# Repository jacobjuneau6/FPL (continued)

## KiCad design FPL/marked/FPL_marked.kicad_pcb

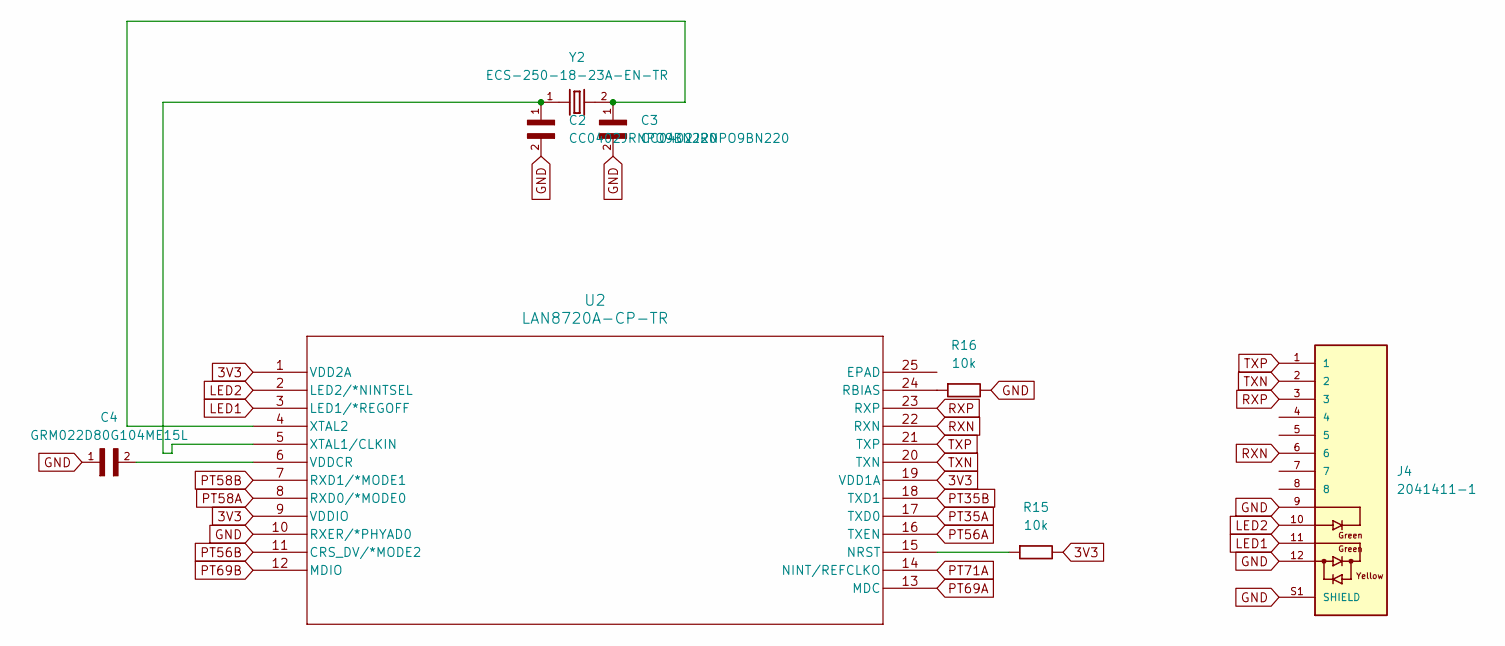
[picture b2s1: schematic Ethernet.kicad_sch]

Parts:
C2, C3: CC0402JRNPO9BN220; CAPC1005X55N; DigiKey_Part_Number 311-1018-1-ND
C4: GRM022D80G104ME15L; CAPC0402X22N; DigiKey_Part_Number 490-10386-1-ND
J4: 2041411-1; TE_2041411-1; PARTREV A; DigiKey_Part_Number A135635CT-ND
R15, R16: 10k; R_Axial_DIN0207_L6.3mm_D2.5mm_P10.16mm_Horizontal
U2: LAN8720A-CP-TR; QFN24-6X6_MC_MCH
Y2: ECS-250-18-23A-EN-TR; XTAL_ECS-250-18-23A-EN-TR; DigiKey_Part_Number XC1671CT-ND

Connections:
3V3: R15.2, U2.1 (VDD2A), U2.9 (VDDIO), U2.19 (VDD1A); also elsewhere on the board
GND: C2.2, C3.2, C4.1, J4.9, J4.12, J4.S1 (SHIELD), J4.S2 (SHIELD), R16.2, U2.10 (RXER/*PHYAD0); also elsewhere on the board
LED1: J4.11, U2.3 (LED1/*REGOFF)
LED2: J4.10, U2.2 (LED2/*NINTSEL)
unnamed: R15.1, U2.15 (NRST)
unnamed: R16.1, U2.24 (RBIAS)
unnamed: C4.2, U2.6 (VDDCR)
unnamed: C2.1, U2.5 (XTAL1/CLKIN), Y2.1
unnamed: C3.1, U2.4 (XTAL2), Y2.2
PT35A: U2.17 (TXD0); also elsewhere on the board
PT35B: U2.18 (TXD1); also elsewhere on the board
PT56A: U2.16 (TXEN); also elsewhere on the board
PT56B: U2.11 (CRS_DV/*MODE2); also elsewhere on the board
PT58A: U2.8 (RXD0/*MODE0); also elsewhere on the board
PT58B: U2.7 (RXD1/*MODE1); also elsewhere on the board
PT69A: U2.13 (MDC); also elsewhere on the board
PT69B: U2.12 (MDIO); also elsewhere on the board
PT71A: U2.14 (NINT/REFCLKO); also elsewhere on the board
RXN: J4.6, U2.22 (RXN)
RXP: J4.3, U2.23 (RXP)
TXN: J4.2, U2.20 (TXN)
TXP: J4.1, U2.21 (TXP)

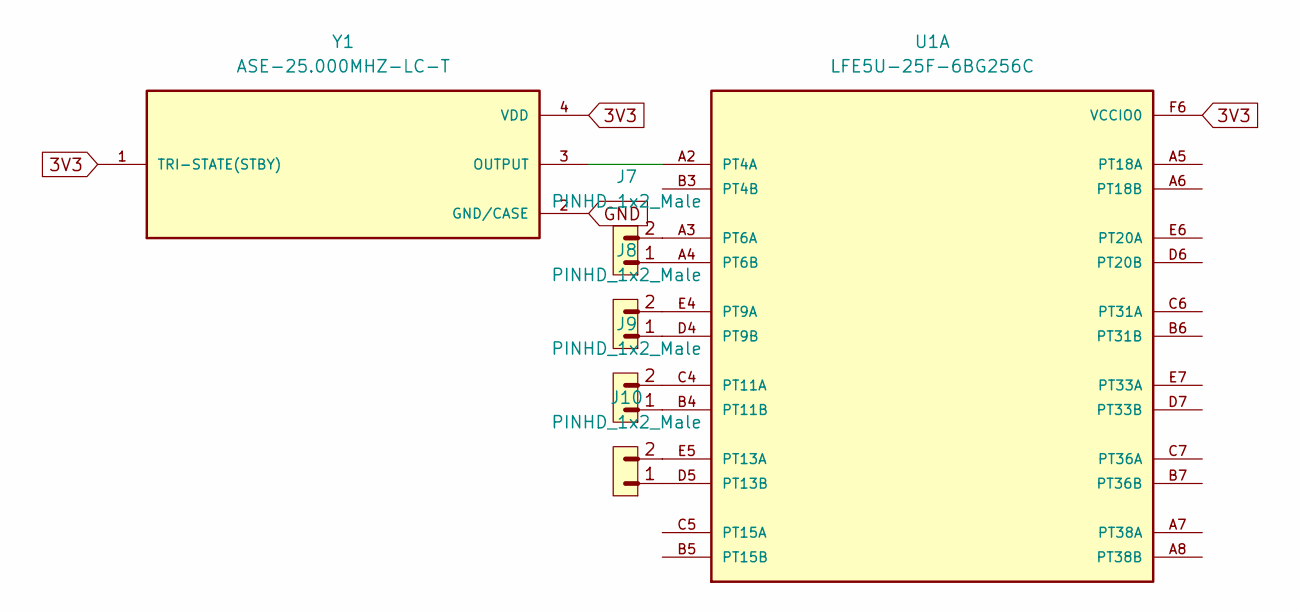
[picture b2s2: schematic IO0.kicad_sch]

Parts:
J7, J8, J9, J10: PINHD_1x2_Male; PinHeader_1x02_P2.54mm_Vertical
U1: LFE5U-25F-6BG256C; BGA256C80P16X16_1400X1400X170; PARTREV 2.8; DigiKey_Part_Number 220-2205-ND
Y1: ASE-25.000MHZ-LC-T; XTAL_ASE-25.000MHZ-LC-T; PARTREV 02-18-22; DigiKey_Part_Number 535-ASE-25.000MHZ-L-C-TCT-ND

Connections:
3V3: U1.F6 (VCCIO0), U1.F7 (VCCIO0), Y1.1 (TRI-STATE(STBY)), Y1.4 (VDD); also elsewhere on the board
GND: Y1.2 (GND/CASE); also elsewhere on the board
unnamed: U1.A2 (PT4A), Y1.3 (OUTPUT)
unnamed: J7.2, U1.A3 (PT6A)
unnamed: J7.1, U1.A4 (PT6B)
unnamed: J8.2, U1.E4 (PT9A)
unnamed: J8.1, U1.D4 (PT9B)
unnamed: J9.2, U1.C4 (PT11A)
unnamed: J9.1, U1.B4 (PT11B)
unnamed: J10.2, U1.E5 (PT13A)
unnamed: J10.1, U1.D5 (PT13B)

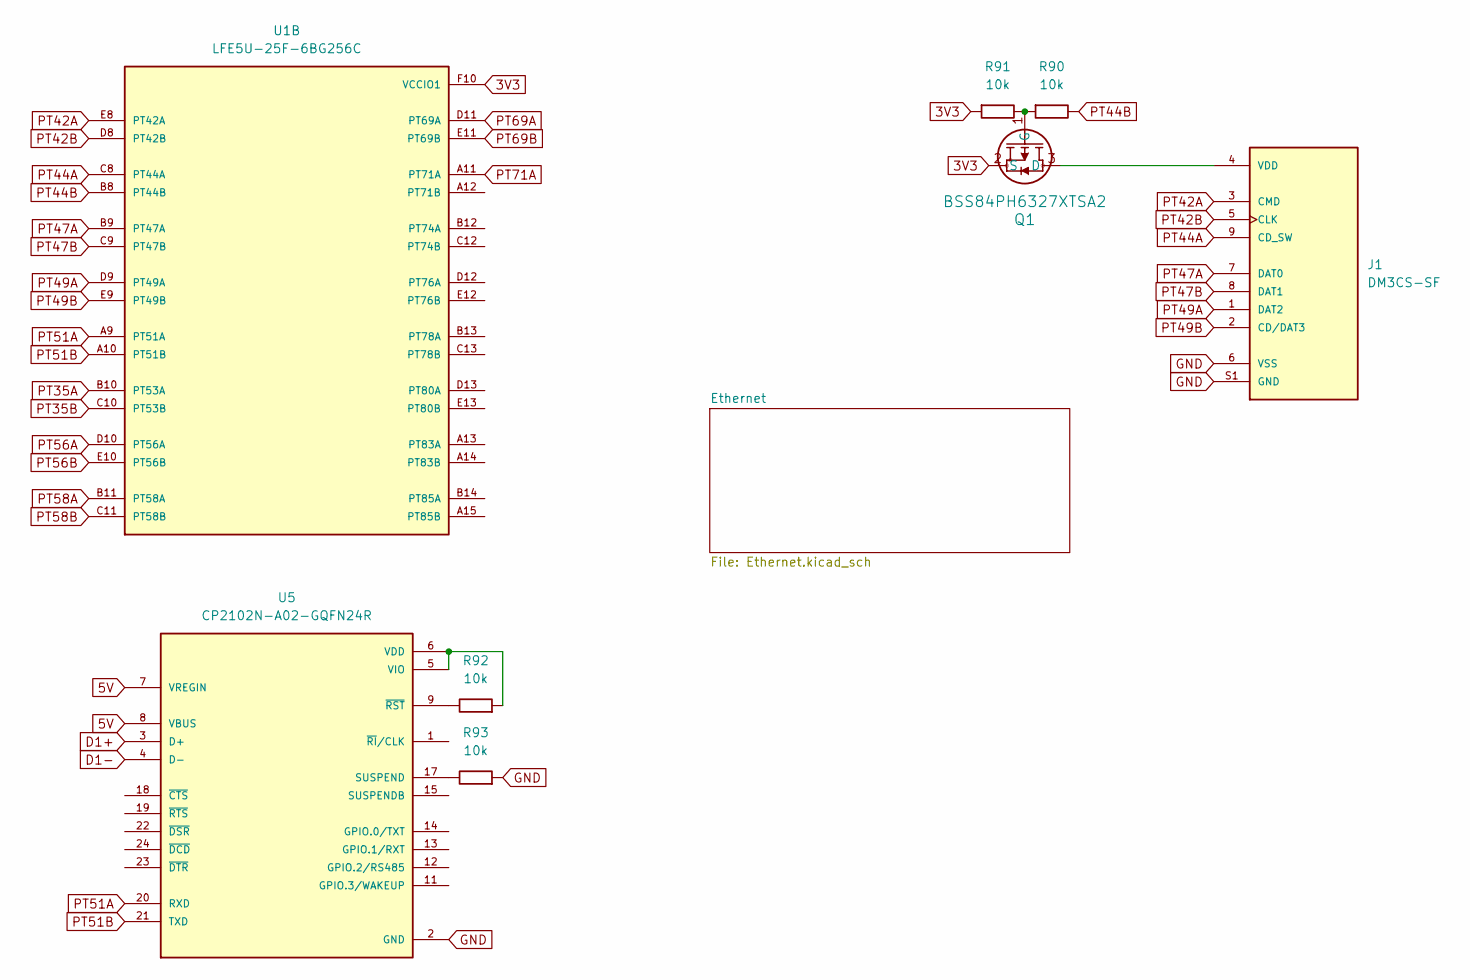
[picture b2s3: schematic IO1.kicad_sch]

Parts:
J1: DM3CS-SF; HRS_DM3CS-SF; PARTREV n/a; DigiKey_Part_Number HR1972CT-ND
Q1: BSS84PH6327XTSA2; SOT23_BSS84_INF; DigiKey_Part_Number BSS84PH6327XTSA2CT-ND
R90, R91, R92, R93: 10k; R_Axial_DIN0207_L6.3mm_D2.5mm_P10.16mm_Horizontal; DigiKey_Part_Number N/A
U1: LFE5U-25F-6BG256C; BGA256C80P16X16_1400X1400X170; PARTREV 2.8; DigiKey_Part_Number 220-2205-ND
U5: CP2102N-A02-GQFN24R; QFN50P400X400X80-25N; PARTREV 1.3; DigiKey_Part_Number 336-5888-1-ND

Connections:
3V3: Q1.2 (S), R91.1, U1.F10 (VCCIO1), U1.F11 (VCCIO1); also elsewhere on the board
5V: U5.7 (VREGIN), U5.8 (VBUS); also elsewhere on the board
D1+: U5.3 (D+); also elsewhere on the board
D1-: U5.4 (D-); also elsewhere on the board
GND: J1.6 (VSS), J1.S1 (GND), J1.S2 (GND), J1.S3 (GND), J1.S5 (GND), R93.1, U5.2 (GND), U5.25 (GND); also elsewhere on the board
unnamed: J1.4 (VDD), Q1.3 (D)
unnamed: Q1.1 (G), R90.1, R91.2
unnamed: R93.2, U5.17 (SUSPEND)
unnamed: R92.1, U5.5 (VIO), U5.6 (VDD)
unnamed: R92.2, U5.9 (~RST)
PT35A: U1.B10 (PT53A); also elsewhere on the board
PT35B: U1.C10 (PT53B); also elsewhere on the board
PT42A: J1.3 (CMD), U1.E8 (PT42A)
PT42B: J1.5 (CLK), U1.D8 (PT42B)
PT44A: J1.9 (CD_SW), U1.C8 (PT44A)
PT44B: R90.2, U1.B8 (PT44B)
PT47A: J1.7 (DAT0), U1.B9 (PT47A)
PT47B: J1.8 (DAT1), U1.C9 (PT47B)
PT49A: J1.1 (DAT2), U1.D9 (PT49A)
PT49B: J1.2 (CD/DAT3), U1.E9 (PT49B)
PT51A: U1.A9 (PT51A), U5.20 (RXD)
PT51B: U1.A10 (PT51B), U5.21 (TXD)
PT56A: U1.D10 (PT56A); also elsewhere on the board
PT56B: U1.E10 (PT56B); also elsewhere on the board
PT58A: U1.B11 (PT58A); also elsewhere on the board
PT58B: U1.C11 (PT58B); also elsewhere on the board
PT69A: U1.D11 (PT69A); also elsewhere on the board
PT69B: U1.E11 (PT69B); also elsewhere on the board
PT71A: U1.A11 (PT71A); also elsewhere on the board

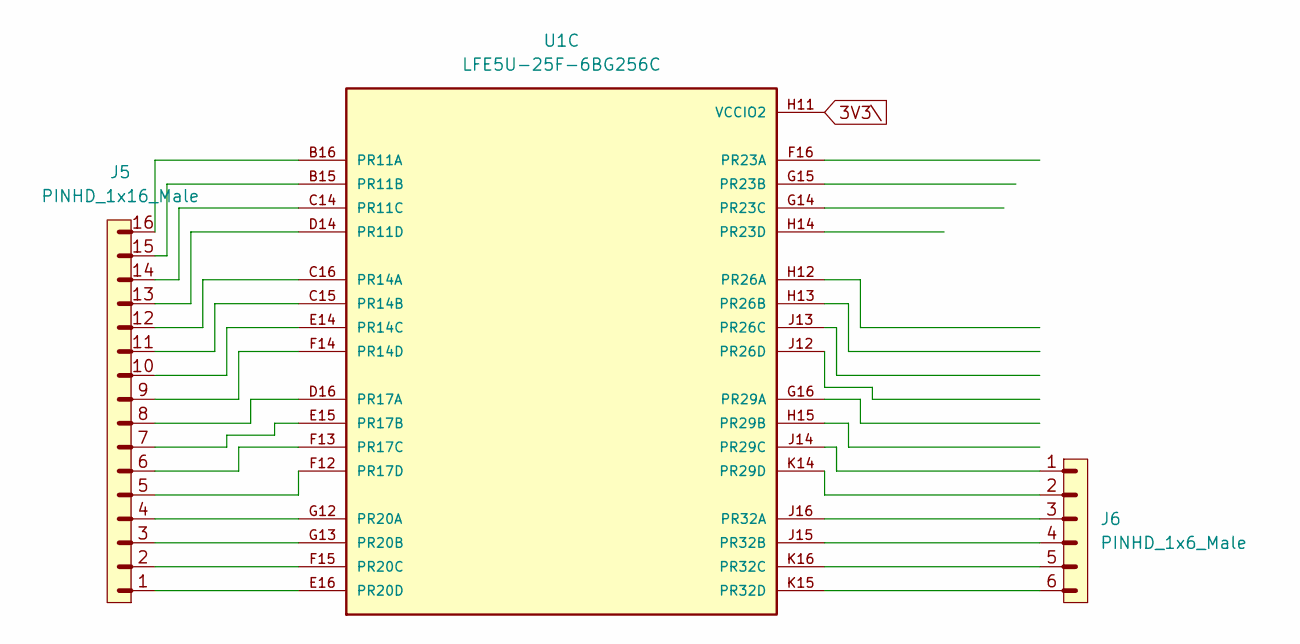
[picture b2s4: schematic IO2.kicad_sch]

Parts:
J5: PINHD_1x16_Male; PinHeader_1x16_P2.54mm_Vertical
J6: PINHD_1x6_Male; PinHeader_1x06_P2.54mm_Vertical
U1: LFE5U-25F-6BG256C; BGA256C80P16X16_1400X1400X170; PARTREV 2.8; DigiKey_Part_Number 220-2205-ND

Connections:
3V3\\: U1.H11 (VCCIO2), U1.J11 (VCCIO2)
unnamed: J5.16, U1.B16 (PR11A)
unnamed: J5.15, U1.B15 (PR11B)
unnamed: J5.14, U1.C14 (PR11C)
unnamed: J5.13, U1.D14 (PR11D)
unnamed: J5.12, U1.C16 (PR14A)
unnamed: J5.11, U1.C15 (PR14B)
unnamed: J5.10, U1.E14 (PR14C)
unnamed: J5.9, U1.F14 (PR14D)
unnamed: J5.8, U1.D16 (PR17A)
unnamed: J5.7, U1.E15 (PR17B)
unnamed: J5.6, U1.F13 (PR17C)
unnamed: J5.5, U1.F12 (PR17D)
unnamed: J5.4, U1.G12 (PR20A)
unnamed: J5.3, U1.G13 (PR20B)
unnamed: J5.2, U1.F15 (PR20C)
unnamed: J5.1, U1.E16 (PR20D)

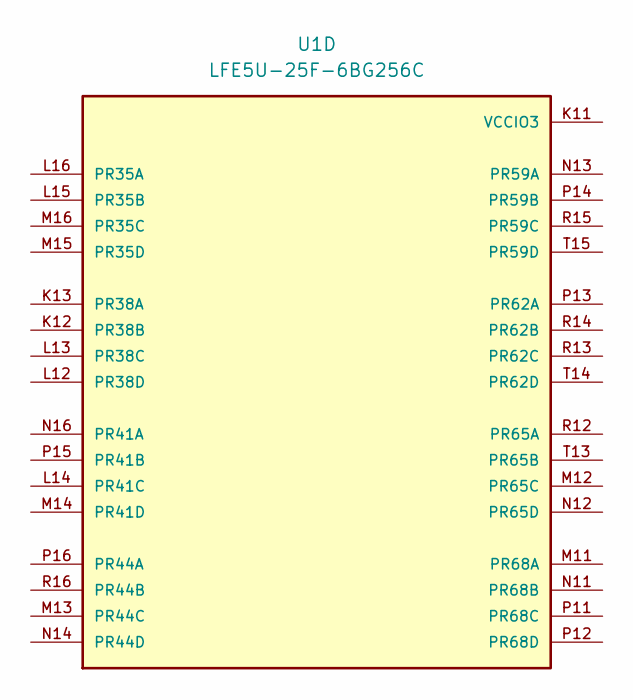
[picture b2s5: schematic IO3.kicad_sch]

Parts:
U1: LFE5U-25F-6BG256C; BGA256C80P16X16_1400X1400X170; PARTREV 2.8; DigiKey_Part_Number 220-2205-ND

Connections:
VCCIO3: U1.K11 (VCCIO3), U1.L11 (VCCIO3)

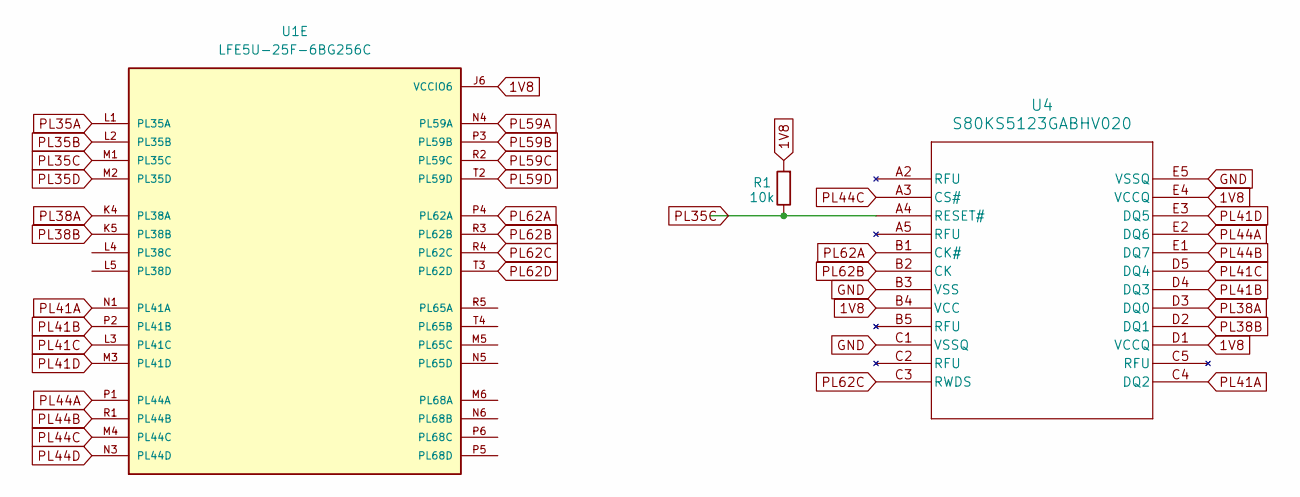
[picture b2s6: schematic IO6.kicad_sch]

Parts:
R1: 10k; R_Axial_DIN0207_L6.3mm_D2.5mm_P10.16mm_Horizontal
U1: LFE5U-25F-6BG256C; BGA256C80P16X16_1400X1400X170; PARTREV 2.8; DigiKey_Part_Number 220-2205-ND
U4: S80KS5123GABHV020; PG-BGA-24-801

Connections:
1V8: R1.1, U1.J6 (VCCIO6), U1.J7 (VCCIO6), U4.B4 (VCC), U4.D1 (VCCQ), U4.E4 (VCCQ); also elsewhere on the board
GND: U4.B3 (VSS), U4.C1 (VSSQ), U4.E5 (VSSQ); also elsewhere on the board
PL35A: U1.L1 (PL35A)
PL35B: U1.L2 (PL35B)
PL35C: R1.2, U1.M1 (PL35C), U4.A4 (RESET#)
PL35D: U1.M2 (PL35D); also elsewhere on the board
PL38A: U1.K4 (PL38A), U4.D3 (DQ0)
PL38B: U1.K5 (PL38B), U4.D2 (DQ1)
PL41A: U1.N1 (PL41A), U4.C4 (DQ2)
PL41B: U1.P2 (PL41B), U4.D4 (DQ3)
PL41C: U1.L3 (PL41C), U4.D5 (DQ4)
PL41D: U1.M3 (PL41D), U4.E3 (DQ5)
PL44A: U1.P1 (PL44A), U4.E2 (DQ6)
PL44B: U1.R1 (PL44B), U4.E1 (DQ7)
PL44C: U1.M4 (PL44C), U4.A3 (CS#)
PL44D: U1.N3 (PL44D)
PL59A: U1.N4 (PL59A)
PL59B: U1.P3 (PL59B)
PL59C: U1.R2 (PL59C)
PL59D: U1.T2 (PL59D)
PL62A: U1.P4 (PL62A), U4.B1 (CK#)
PL62B: U1.R3 (PL62B), U4.B2 (CK)
PL62C: U1.R4 (PL62C), U4.C3 (RWDS)
PL62D: U1.T3 (PL62D)

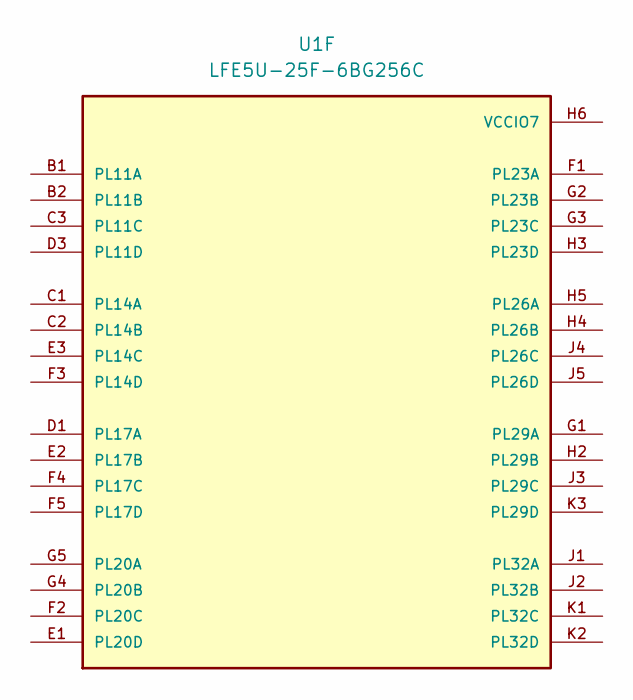
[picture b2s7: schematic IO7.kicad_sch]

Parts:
U1: LFE5U-25F-6BG256C; BGA256C80P16X16_1400X1400X170; PARTREV 2.8; DigiKey_Part_Number 220-2205-ND

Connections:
VCCIO7: U1.H6 (VCCIO7), U1.H7 (VCCIO7)

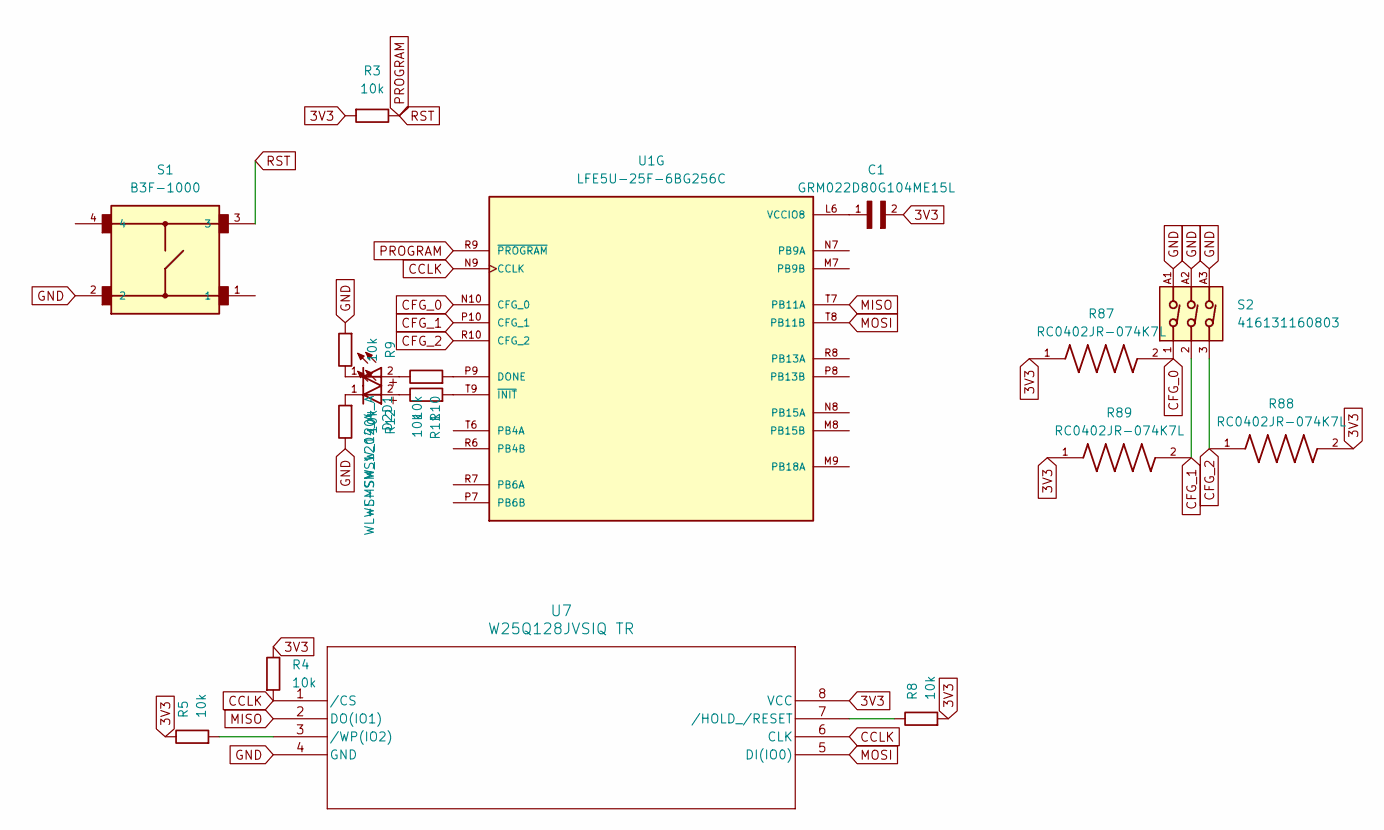
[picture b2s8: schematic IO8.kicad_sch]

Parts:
C1: GRM022D80G104ME15L; CAPC0402X22N; DigiKey_Part_Number 490-10386-1-ND
D1, D2: WL-SMSW_1204_A; DigiKey_Part_Number 732-12022-1-ND
R3, R9, R10, R11, R12: 10k; R_Axial_DIN0207_L6.3mm_D2.5mm_P10.16mm_Horizontal; DigiKey_Part_Number N/A
R4, R5, R8: 10k; R_Axial_DIN0207_L6.3mm_D2.5mm_P10.16mm_Horizontal
R87, R88, R89: RC0402JR-074K7L; RC0402N_YAG; DigiKey_Part_Number 311-4.7KJRCT-ND
S1: B3F-1000; SW_B3F-1000; DigiKey_Part_Number SW400-ND
S2: 416131160803; DigiKey_Part_Number 732-416131160803CT-ND
U1: LFE5U-25F-6BG256C; BGA256C80P16X16_1400X1400X170; PARTREV 2.8; DigiKey_Part_Number 220-2205-ND
U7: W25Q128JVSIQ TR; SOIC_208MIL_WIN; DigiKey_Part_Number 256-W25Q128JVSIQTRCT-ND

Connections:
3V3: C1.2, R3.1, R4.2, R5.2, R8.1, R87.1, R88.2, R89.1, U7.8 (VCC); also elsewhere on the board
CCLK: R4.1, U1.N9 (CCLK), U7.1 (/CS), U7.6 (CLK)
CFG_0: R87.2, S2.1, U1.N10 (CFG_0)
CFG_1: R89.2, S2.2, U1.P10 (CFG_1)
CFG_2: R88.1, S2.3, U1.R10 (CFG_2)
GND: R9.1, R12.2, S1.2, S2.A1, S2.A2, S2.A3, U7.4 (GND); also elsewhere on the board
MISO: U1.T7 (PB11A), U7.2 (DO(IO1))
MOSI: U1.T8 (PB11B), U7.5 (DI(IO0))
unnamed: D1.1, R9.2
unnamed: D1.2, R10.2
unnamed: D2.1, R12.1
unnamed: D2.2, R11.2
unnamed: R10.1, U1.P9 (DONE)
unnamed: C1.1, U1.L6 (VCCIO8)
unnamed: R11.1, U1.T9 (~INIT)
unnamed: R8.2, U7.7 (/HOLD_/RESET)
unnamed: R5.1, U7.3 (/WP(IO2))
PROGRAM: R3.2, S1.3, U1.R9 (~PROGRAM)

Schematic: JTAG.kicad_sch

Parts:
J3: PINHD_1x6_Male; PinHeader_1x06_P2.54mm_Vertical
R13, R14: 10k; R_Axial_DIN0207_L6.3mm_D2.5mm_P10.16mm_Horizontal
U1: LFE5U-25F-6BG256C; BGA256C80P16X16_1400X1400X170; PARTREV 2.8; DigiKey_Part_Number 220-2205-ND

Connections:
1V2: J3.5; also elsewhere on the board
3V3: R13.1, R14.1; also elsewhere on the board
GND: J3.6; also elsewhere on the board
unnamed: J3.4, U1.T10 (TCK)
unnamed: J3.2, R14.2, U1.R11 (TDI)
unnamed: J3.3, U1.M10 (TDO)
unnamed: J3.1, R13.2, U1.T11 (TMS)

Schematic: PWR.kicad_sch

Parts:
C5, C6: GRM022D80G104ME15L; CAPC0402X22N; DigiKey_Part_Number 490-10386-1-ND
J18, J19, J20, J21, J22: PINHD_1x5_Male; PinHeader_1x05_P2.54mm_Vertical
U1: LFE5U-25F-6BG256C; BGA256C80P16X16_1400X1400X170; PARTREV 2.8; DigiKey_Part_Number 220-2205-ND

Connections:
1V2: C5.2, J18.1, J18.2, J18.3, J18.4, J18.5; also elsewhere on the board
1V8: C6.2, J19.1, J19.2, J19.3, J19.4, J19.5; also elsewhere on the board
2V5: J21.1, J21.2, J21.3, J21.4, J21.5; also elsewhere on the board
3V3: J20.1, J20.2, J20.3, J20.4, J20.5; also elsewhere on the board
GND: J22.1, J22.2, J22.3, J22.4, J22.5, U1.A1 (GND1), U1.A16 (GND1), U1.D2 (GND1), U1.D15 (GND1), U1.F8 (GND1), U1.F9 (GND1), U1.G8 (GND1), U1.G10 (GND1), U1.H1 (GND1), U1.H8 (GND1), U1.H9 (GND1), U1.H10 (GND1), U1.H16 (GND1), U1.J8 (GND2), U1.J9 (GND2), U1.J10 (GND2), U1.K6 (GND2), U1.K7 (GND2), U1.K8 (GND2), U1.K9 (GND2), U1.K10 (GND2), U1.N2 (GND2), U1.N15 (GND2), U1.T1 (GND2), U1.T5 (GND2), U1.T12 (GND2), U1.T16 (GND2); also elsewhere on the board
VCC: C5.1, U1.G6 (VCC), U1.G7 (VCC), U1.G9 (VCC), U1.L8 (VCC), U1.L9 (VCC), U1.L10 (VCC)
VCCAUX: C6.1, U1.G11 (VCCAUX), U1.L7 (VCCAUX)

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
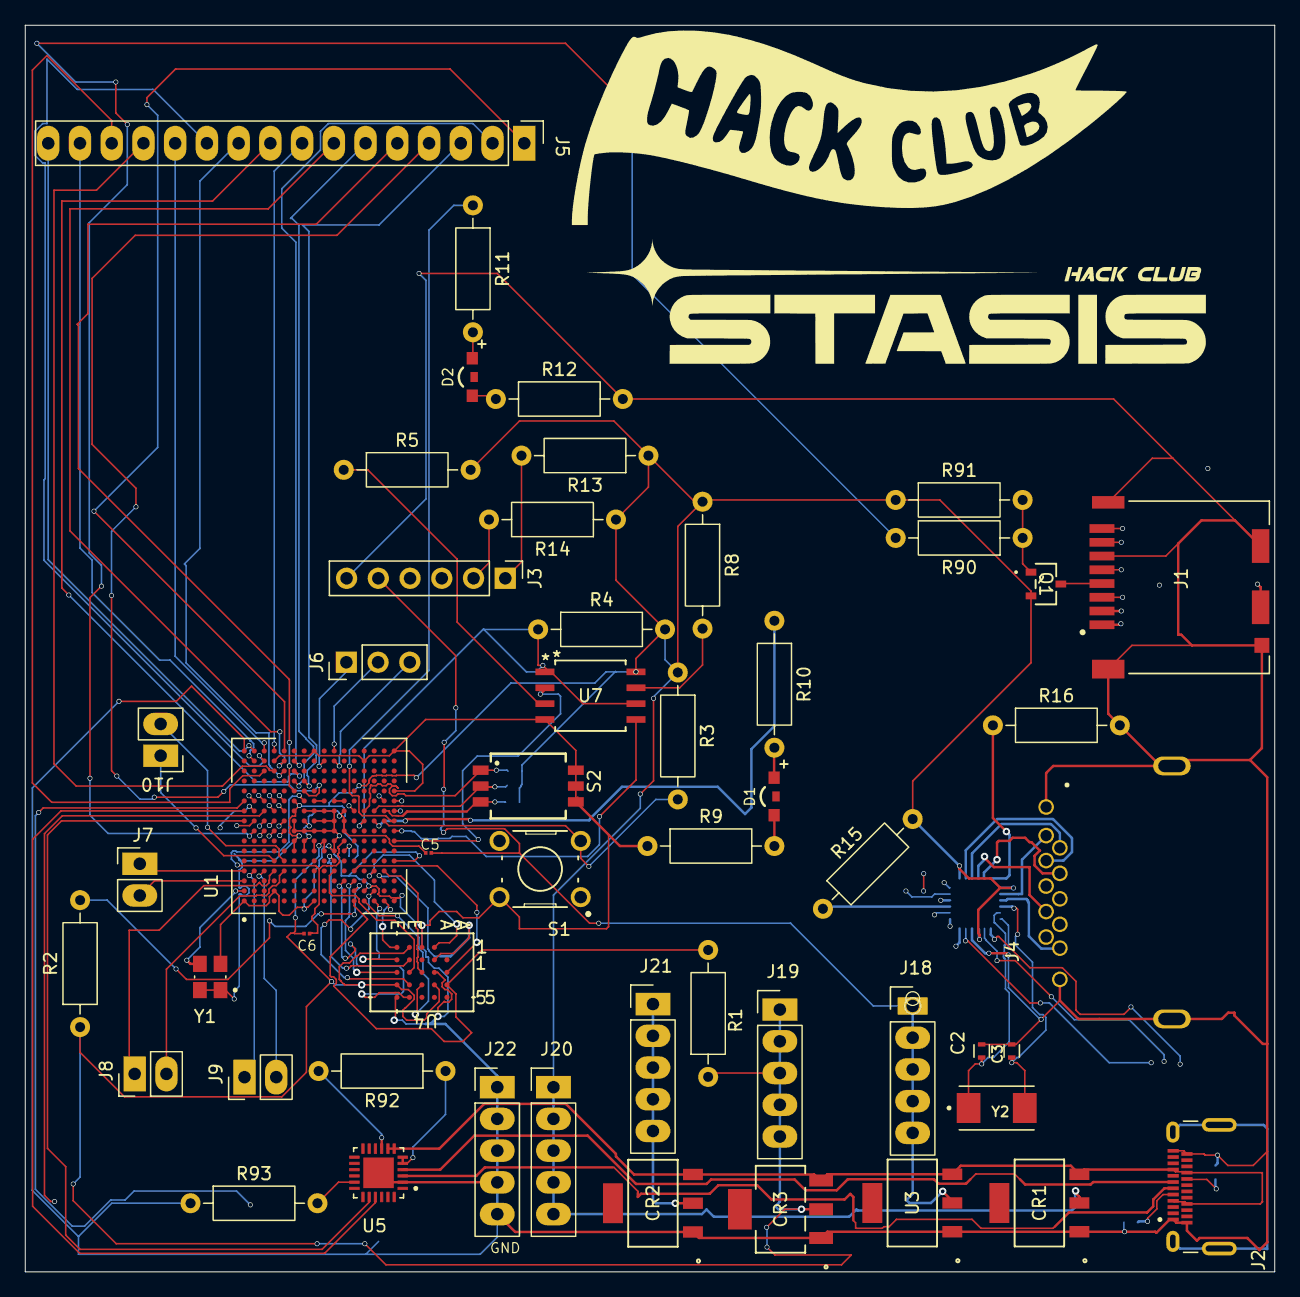
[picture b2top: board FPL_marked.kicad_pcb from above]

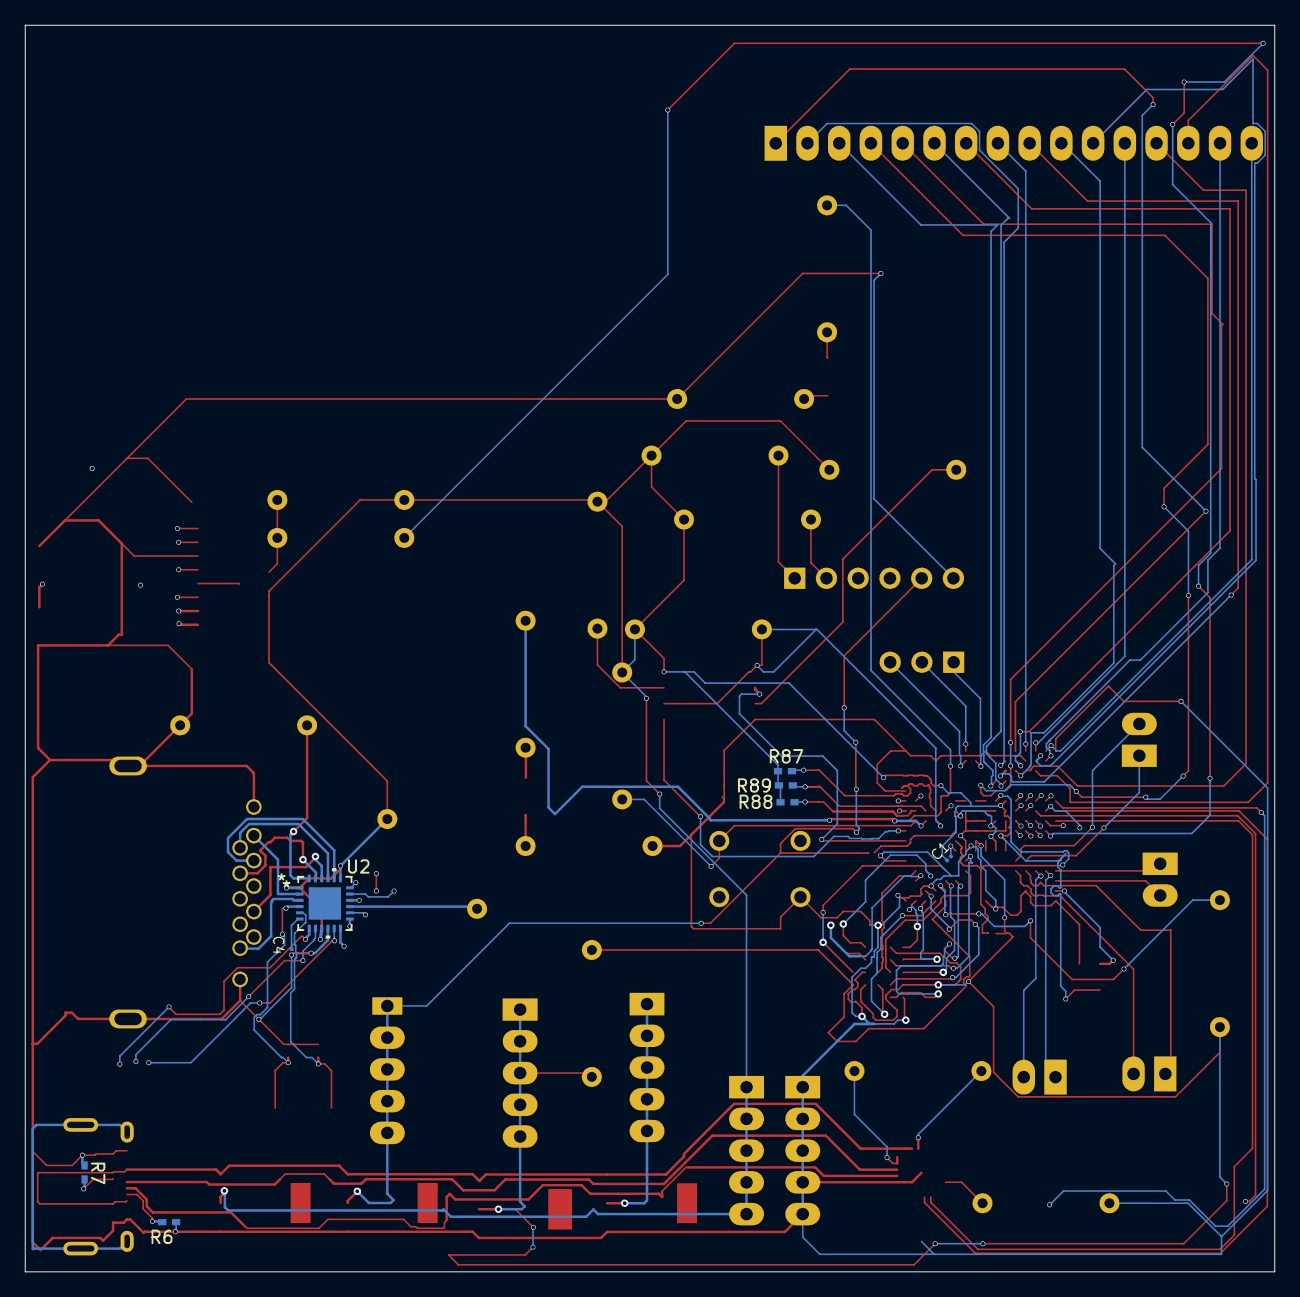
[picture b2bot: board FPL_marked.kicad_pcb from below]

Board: 4 copper layers, 100.0 x 99.8 mm, 60 parts (8 on the bottom side), 113 nets.

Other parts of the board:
CR1: LD1117S33CTR; SOT-223_STM
CR2: LD1117S25CTR; SOT-223_STM
CR3: LD1117S18TR; SOT-223_STM-M
J2: CX90BW1-24P1; HIROSE_CX90BW1-24P1
R2: 10k; R_Axial_DIN0207_L6.3mm_D2.5mm_P10.16mm_Horizontal
R6, R7: RC0402FR-075K1L; RC0402N_YAG
U3: LD1117S12CTR; SOT-223_STM

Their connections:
1V2: U3.2 (VOUT); also elsewhere on the board
1V8: CR3.2 (VOUT), R2.1; also elsewhere on the board
2V5: CR2.2 (VOUT); also elsewhere on the board
3V3: CR1.2 (VOUT); also elsewhere on the board
5V: CR1.3 (VIN), CR2.3 (VIN), CR3.3 (VIN), J2.A4 (VBUS_A), J2.A9 (VBUS_A), J2.B4 (VBUS_B), J2.B9 (VBUS_B), U3.3 (VIN); also elsewhere on the board
D1+: J2.A6 (D1+); also elsewhere on the board
D1-: J2.A7 (D1-); also elsewhere on the board
GND: CR1.1 (ADJ/GND), CR2.1 (ADJ/GND), CR3.1 (ADJ/GND), J2.A1 (GND_A), J2.A12 (GND_A), J2.B1 (GND_B), J2.B12 (GND_B), R6.2, R7.1, U3.1 (ADJ/GND); also elsewhere on the board
unnamed: J2.A5 (CC1), R6.1
unnamed: J2.B5 (CC2), R7.2
unnamed: J2.SH1 (SHIELD), J2.SH2 (SHIELD), J2.SH3 (SHIELD), J2.SH4 (SHIELD)
PL35D: R2.2; also elsewhere on the board

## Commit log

2026-04-07 add PCB and toolchain configs
2026-04-07 remove bad Litex
2026-04-07 WIP SoC
2026-04-08 code
2026-04-08 readme
2026-04-08 3d model
2026-04-10 BOM updates and readme updates , mainanence, code
